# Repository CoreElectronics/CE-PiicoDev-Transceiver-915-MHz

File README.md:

# PiicoDev® Transceiver

This is the repo for the Core Electronics [PiicoDev Transceiver](https://core-electronics.com.au/catalog/product/view/sku/CE08757).

## License
This project is open source - please review the LICENSE.md file for further licensing information.

If you have any technical questions, or concerns about licensing, please contact technical support on the [Core Electronics forums](https://forum.core-electronics.com.au/).

*\"PiicoDev\" and the PiicoDev logo are trademarks of Core Electronics Pty Ltd.*

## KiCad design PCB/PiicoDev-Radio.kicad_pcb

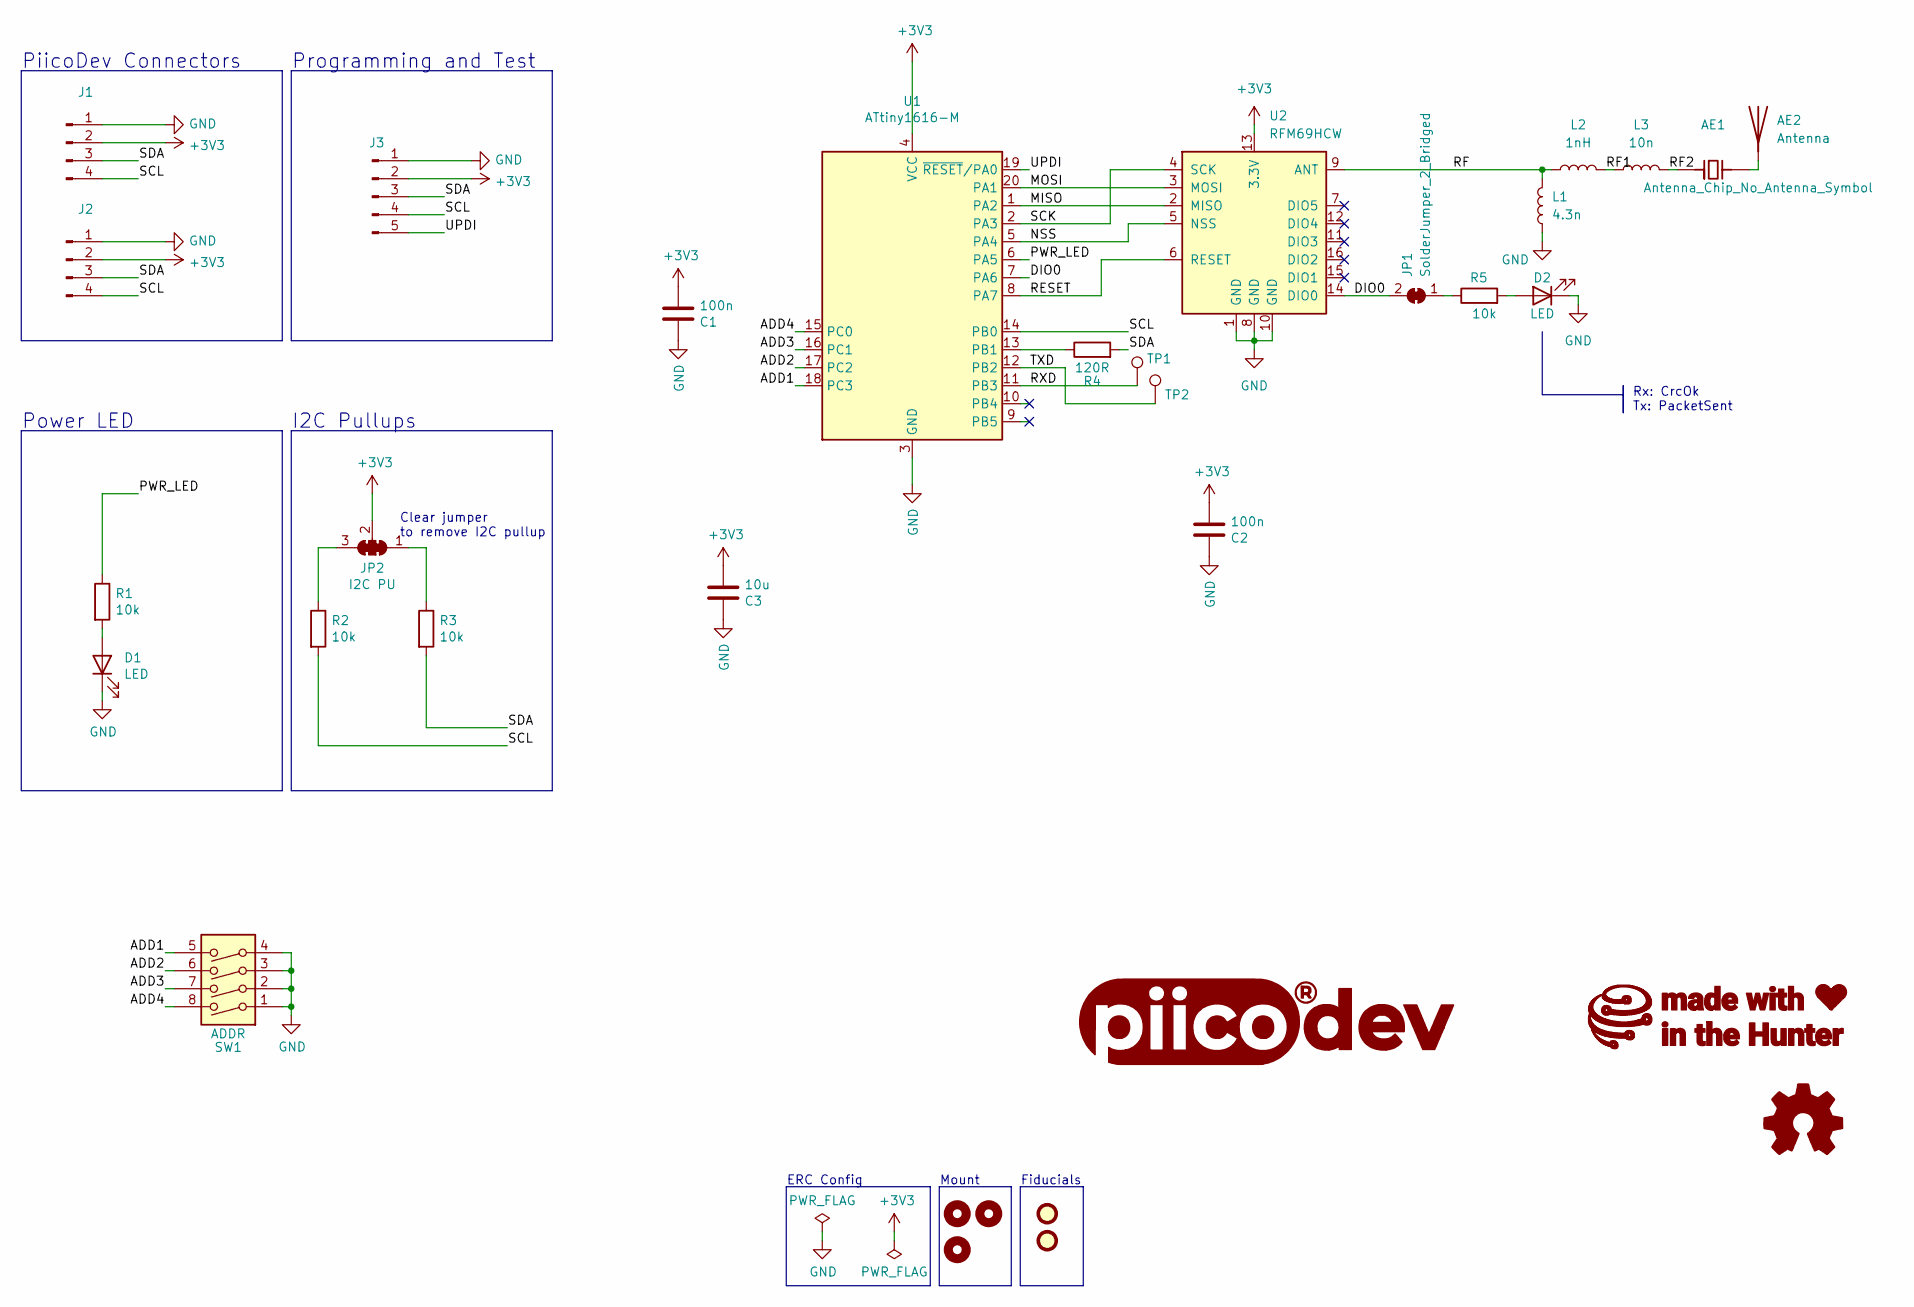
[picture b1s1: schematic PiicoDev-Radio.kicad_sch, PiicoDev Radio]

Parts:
AE1: Antenna_Chip_No_Antenna_Symbol; Antenna_Chip_TDK_ANT160920ST-1204A1
AE2: Antenna; PiicoDev_Radio_Antenna
C1, C2: 100n; C_0402_1005Metric
C3: 10u; C_0603_1608Metric
D1, D2: LED; LED_0603_1608Metric
FID1, FID2: Fiducial; Fiducial_1mm_Mask2mm
G1: LOGO_PiicoDev; piicodev_logo_14.2x3.4mm
G2: LOGO_CoreElectronics_no-text; CoreElectronics_logo_5mm_v2
G3: LOGO_made-with-love; piicodev_logo_14.2x3.4mm
H1, H2, H3: MountingHole; MountingHole_2.7mm_M2.5_PadClearance_1.2
J1, J2: JST_SH_SM04B-SRSS-TB_1x04-1MP_P1.00mm_Horizontal
J3: Conn_01x05_Male; TestPoint_Pad_D1.0mm_x05_Pattern1
JP1: SolderJumper_2_Bridged; SolderJumper-2_P1.3mm_Bridged_RoundedPad1.0x1.5mm
JP2: I2C PU; SolderJumper-3_P1.3mm_Closed_RoundedPad1.0x1.5mm_NumberLabe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
L1: 4.3n; L_0402_1005Metric
L2: 1nH; L_0402_1005Metric
L3: 10n; L_0402_1005Metric
LOGO1: Logo_Open_Hardware_Small; oshw
R1, R2, R3, R5: 10k; R_0402_1005Metric
R4: 120R; R_0402_1005Metric
SW1: ADDR; SW_DIP_x04_Slide_CHS-04A1
TP1, TP2: TestPoint; TestPoint_Pad_1.5x1.5mm
U1: ATtiny1616-M; VQFN-20-1EP_3x3mm_P0.4mm_EP1.7x1.7mm
U2: RFM69HCW; HOPERF_RFM69HCW_SMD

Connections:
+3V3: C1.2, C2.2, C3.2, J1.2, J2.2, J3.2, JP2.2 (C), U1.4 (VCC), U2.13 (3.3V)
/ADD1: SW1.5, U1.18 (PC3)
/ADD2: SW1.6, U1.17 (PC2)
/ADD3: SW1.7, U1.16 (PC1)
/ADD4: SW1.8, U1.15 (PC0)
/DIO0: JP1.2 (B), U1.7 (PA6), U2.14 (DIO0)
/MISO: U1.1 (PA2), U2.2 (MISO)
/MOSI: U1.20 (PA1), U2.3 (MOSI)
/NSS: U1.5 (PA4), U2.5 (NSS)
/PWR_LED: R1.1, U1.6 (PA5)
/RESET: U1.8 (PA7), U2.6 (RESET)
/RF: L1.2, L2.1, U2.9 (ANT)
/RF1: L2.2, L3.1
/RF2: AE1.4 (FEED), L3.2
/RXD: TP1.1, U1.11 (PB3)
/SCK: U1.2 (PA3), U2.4 (SCK)
/SCL: J1.4, J2.4, J3.4, R2.2, U1.14 (PB0)
/SDA: J1.3, J2.3, J3.3, R3.2, R4.2
/TXD: TP2.1, U1.12 (PB2)
/UPDI: J3.5, U1.19 (~RESET/PA0)
GND: C1.1, C2.1, C3.1, D1.1 (K), D2.1 (K), J1.1, J2.1, J3.1, L1.1, SW1.1, SW1.2, SW1.3, SW1.4, U1.3 (GND), U1.21 (GND), U2.1 (GND), U2.8 (GND), U2.10 (GND)
unnamed: AE1.1 (PCB_Trace), AE2.1 (A)
unnamed: D1.2 (A), R1.2
unnamed: D2.2 (A), R5.2
unnamed: JP1.1 (A), R5.1
unnamed: JP2.1 (A), R3.1
unnamed: JP2.3 (B), R2.1
unnamed: R4.1, U1.13 (PB1)

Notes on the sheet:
PiicoDev Connectors
I2C Pullups
Power LED
Rx: CrcOk Tx: PacketSent
Mount
Clear jumper to remove I2C pullup
Programming and Test
ERC Config
Fiducials

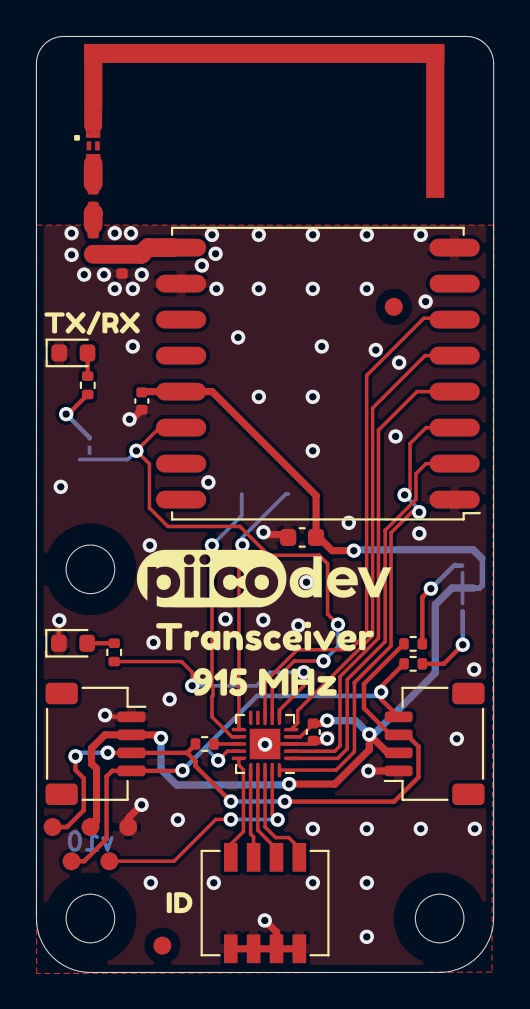
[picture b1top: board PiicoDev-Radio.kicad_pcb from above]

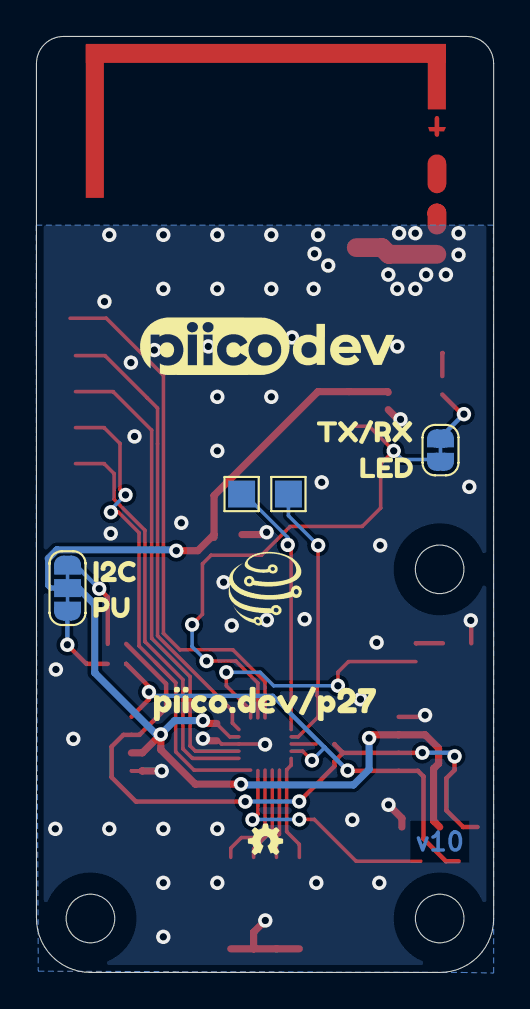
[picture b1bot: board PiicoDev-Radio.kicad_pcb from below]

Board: 2 copper layers, 25.4 x 52.0 mm, 41 parts (10 on the bottom side), 28 nets.

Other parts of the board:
kibuzzard-637C5B84: G***; kibuzzard-637C5B84
kibuzzard-637C5BCC: G***; kibuzzard-637C5BCC
kibuzzard-637C5BDE: G***; kibuzzard-637C5BDE
kibuzzard-637C5DFB: G***; kibuzzard-637C5DFB
kibuzzard-637C5EAE: G***; kibuzzard-637C5EAE
kibuzzard-637C5EDA: G***; kibuzzard-637C5EDA
kibuzzard-637C5F9F: G***; kibuzzard-637C5F9F

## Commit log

2022-08-11 Create KiCad project
2022-08-18 Basic design complete
2022-09-07 Add jumpers to allow external pull-up resistors
2022-11-10 Remove SMA and add PCB antenna
2022-11-16 Improve F.Fab layer
2022-11-17 Change R5 to 1k
2022-12-07 v10 Improve RFM69HCW footprint
2022-12-13 Update chip antenna footprint
2023-01-04 exclude artwork components from BOM + .pos files
2023-01-09 rename schematic pdf

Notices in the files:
PCB/PiicoDev-Radio.kicad_sch:
License: CCASAv4.0 http://creativecommons.org/licenses/by-sa/4.0
